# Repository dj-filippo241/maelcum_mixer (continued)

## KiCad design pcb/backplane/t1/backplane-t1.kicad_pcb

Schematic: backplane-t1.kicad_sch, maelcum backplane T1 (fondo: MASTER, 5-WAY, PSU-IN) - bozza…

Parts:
C1, C3, C5, C7, C9, C11, C13, C15, C17, C19, C21, C23, C25, C27, C29, C31, C33, C35, C37, C39, C41, C43, C45, C47, C49, C51, C53, C55: 100n 50V; C_0805_2012Metric
C2, C4, C6, C8, C10, C12, C14, C16, C18, C20, C22, C24, C26, C28, C30, C32, C34, C36, C38, C40, C42, C44, C46, C48, C50, C52, C54, C56: 10u 50V X7R; C_1206_3216Metric
F1, F2: PTC 0.3 A; Fuse_1812_4532Metric
F3, F4, F5, F6, F7, F8: PTC 0.2 A; Fuse_1812_4532Metric
F9, F14, F19, F24: PTC 0.1 A; Fuse_1812_4532Metric
F10, F12, F15, F17, F20, F22, F25, F27: PTC 0.05 A; Fuse_1812_4532Metric
F11, F13, F16, F18, F21, F23, F26, F28: PTC 0.5 A; Fuse_1812_4532Metric
H1, H2, H3, H4, H5: CHASSIS; MountingHole_3.2mm_M3_Pad
J5W: ponticello J5W; PinHeader_2x02_P2.54mm_Vertical
J5W1: C96 femmina 5W1; DIN41612_C_3x32_Female_Vertical_THT
J5W2: C96 femmina 5W2; DIN41612_C_3x32_Female_Vertical_THT
J5W3: C96 femmina 5W3; DIN41612_C_3x32_Female_Vertical_THT
J5W4: C96 femmina 5W4; DIN41612_C_3x32_Female_Vertical_THT
JC1: cavo C1 T1-T2 (VE); IDC-Header_2x05_P2.54mm_Vertical
JC2: cavo C2 T1-T2 (pilotato); IDC-Header_2x05_P2.54mm_Vertical
JC5: cavo C5 T1-T4 (VE); IDC-Header_2x05_P2.54mm_Vertical
JC6: cavo C6 T1-T4 (pilotato); IDC-Header_2x10_P2.54mm_Vertical
JMAS: C96 femmina MAS; DIN41612_C_3x32_Female_Vertical_THT
JMS: ponticello JMS; PinHeader_2x02_P2.54mm_Vertical
JOUT_L: C96 femmina OUT_L; DIN41612_C_3x32_Female_Vertical_THT
JOUT_R: C96 femmina OUT_R; DIN41612_C_3x32_Female_Vertical_THT
JP2: potenza P2 T1-T2; Molex_Mini-Fit_Jr_5566-10A2_2x05_P4.20mm_Vertical
JP3: potenza P3 T1-T3; Molex_Mini-Fit_Jr_5566-10A2_2x05_P4.20mm_Vertical
JP4: potenza P4 T1-T4; Molex_Mini-Fit_Jr_5566-10A2_2x05_P4.20mm_Vertical
JPSU: C96 femmina PSU; DIN41612_C_3x32_Female_Vertical_THT
JVIE: presa JVIE; PinHeader_1x03_P2.54mm_Vertical

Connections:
5W_OUT_L: J5W.1, J5W1.b4
5W_OUT_R: J5W.3, J5W2.b5
5W_SUM_L: J5W1.b7, J5W3.b7
5W_SUM_R: J5W2.b8, J5W4.b8
+5V: F3.1, F6.1, F9.1, F14.1, F19.1, F24.1, JP2.5, JP3.5, JP4.5, JPSU.a21, JPSU.a22
+5V_5W1: C17.1, C18.1, F9.2, J5W1.a21, J5W1.a22
+5V_5W2: C27.1, C28.1, F14.2, J5W2.a21, J5W2.a22
+5V_5W3: C37.1, C38.1, F19.2, J5W3.a21, J5W3.a22
+5V_5W4: C47.1, C48.1, F24.2, J5W4.a21, J5W4.a22
+5V_OUT_L: C5.1, C6.1, F3.2, JOUT_L.a21, JOUT_L.a22
+5V_OUT_R: C11.1, C12.1, F6.2, JOUT_R.a21, JOUT_R.a22
AC_OK: JOUT_L.c17, JPSU.c17
AGND: C1.2, C2.2, C3.1, C4.1, C5.2, C6.2, C7.2, C8.2, C9.1, C10.1, C11.2, C12.2, C13.2, C14.2, C15.1, C16.1, C17.2, C18.2, C19.2, C20.2, C21.2, C22.2, C23.1, C24.1, C25.1, C26.1, C27.2, C28.2, C29.2, C30.2, C31.2, C32.2, C33.1, C34.1, C35.1, C36.1, C37.2, C38.2, C39.2, C40.2, C41.2, C42.2, C43.1, C44.1, C45.1, C46.1, C47.2, C48.2, C49.2, C50.2, C51.2, C52.2, C53.1, C54.1, C55.1, C56.1, J5W1.a13, J5W1.a14, J5W1.a15, J5W1.a16, J5W1.a17, J5W1.a18, J5W1.a19, J5W1.a20, J5W1.b3, J5W1.b6, J5W1.b9, J5W1.b12, J5W1.b15, J5W1.b18, J5W1.b21, J5W1.b24, J5W1.b27, J5W1.b30, J5W2.a13, J5W2.a14, J5W2.a15, J5W2.a16, J5W2.a17, J5W2.a18, J5W2.a19, J5W2.a20, J5W2.b3, J5W2.b6, J5W2.b9, J5W2.b12, J5W2.b15, J5W2.b18, J5W2.b21, J5W2.b24, J5W2.b27, J5W2.b30, J5W3.a13, J5W3.a14, J5W3.a15, J5W3.a16, J5W3.a17, J5W3.a18, J5W3.a19, J5W3.a20, J5W3.b3, J5W3.b6, J5W3.b9, J5W3.b12, J5W3.b15, J5W3.b18, J5W3.b21, J5W3.b24, J5W3.b27, J5W3.b30, J5W4.a13, J5W4.a14, J5W4.a15, J5W4.a16, J5W4.a17, J5W4.a18, J5W4.a19, J5W4.a20, J5W4.b3, J5W4.b6, J5W4.b9, J5W4.b12, J5W4.b15, J5W4.b18, J5W4.b21, J5W4.b24, J5W4.b27, J5W4.b30, JC1.1, JC1.3, JC1.5, JC1.6, JC1.7, JC1.8, JC1.9, JC1.10, JC2.1, JC2.3, JC2.7, JC2.8, JC2.9, JC2.10, JC5.1, JC5.3, JC5.5, JC5.7, JC5.9, JC5.10, JC6.1, JC6.3, JC6.5, JC6.7, JC6.9, JC6.11, JC6.13, JC6.15, JC6.19, JC6.20, JMAS.a13, JMAS.a14, JMAS.a15, JMAS.a16, JMAS.a17, JMAS.a18, JMAS.a19, JMAS.a20, JMAS.b3, JMAS.b6, JMAS.b9, JMAS.b12, JMAS.b15, JMAS.b18, JMAS.b21, JMAS.b24, JMAS.b27, JMAS.b30, JOUT_L.a13, JOUT_L.a14, JOUT_L.a15, JOUT_L.a16, JOUT_L.a17, JOUT_L.a18, JOUT_L.a19, JOUT_L.a20, JOUT_R.a13, JOUT_R.a14, JOUT_R.a15, JOUT_R.a16, JOUT_R.a17, JOUT_R.a18, JOUT_R.a19, JOUT_R.a20, JP2.6, JP2.7, JP2.8, JP3.6, JP3.7, JP3.8, JP4.6, JP4.7, JP4.8, JPSU.a13, JPSU.a14, JPSU.a15, JPSU.a16, JPSU.a17, JPSU.a18, JPSU.a19, JPSU.a20, JVIE.2
CHASSIS: H1.1, H2.1, H3.1, H4.1, H5.1, J5W1.a25, J5W1.a26, J5W2.a25, J5W2.a26, J5W3.a25, J5W3.a26, J5W4.a25, J5W4.a26, JMAS.a25, JMAS.a26, JOUT_L.a25, JOUT_L.a26, JOUT_R.a25, JOUT_R.a26, JP2.10, JP3.10, JP4.10, JPSU.a25, JPSU.a26
CTRL_GND: J5W1.a23, J5W1.a24, J5W1.c16, J5W1.c20, J5W1.c24, J5W1.c28, J5W2.a23, J5W2.a24, J5W2.c16, J5W2.c20, J5W2.c24, J5W2.c28, J5W3.a23, J5W3.a24, J5W3.c16, J5W3.c20, J5W3.c24, J5W3.c28, J5W4.a23, J5W4.a24, J5W4.c16, J5W4.c20, J5W4.c24, J5W4.c28, JC2.5, JC6.17, JMAS.c16, JMAS.c20, JMAS.c24, JMAS.c28, JOUT_L.a23, JOUT_L.a24, JOUT_L.c16, JOUT_L.c20, JOUT_L.c24, JOUT_L.c28, JOUT_R.a23, JOUT_R.a24, JOUT_R.c16, JOUT_R.c20, JOUT_R.c24, JOUT_R.c28, JP2.9, JP3.9, JP4.9, JPSU.a23, JPSU.a24, JPSU.c16, JPSU.c20, JPSU.c24, JPSU.c28
DJBUS_L: J5W3.b1, JC1.2
DJBUS_R: J5W4.b2, JC1.4
GLOBAL_MUTE: JC2.6, JC6.18, JOUT_L.c9, JOUT_R.c9
INS_RET_L: JMAS.b28, JMS.2
INS_RET_R: JMAS.b29, JMS.4
INS_SEND_L: JMAS.b25, JMS.1
INS_SEND_R: JMAS.b26, JMS.3
MON_L: JC2.2, JMAS.b22
MON_R: JC2.4, JMAS.b23
MSUM1_L: J5W.2, JMAS.b1
MSUM1_R: J5W.4, JMAS.b2
MSUM2_L: JC6.2, JMAS.b4
MSUM2_R: JC6.4, JMAS.b5
MSUM3_L: JC6.6, JMAS.b7
MSUM3_R: JC6.8, JMAS.b8
MSUM4_L: JC6.10, JMAS.b10
MSUM4_R: JC6.12, JMAS.b11
MSUM5_L: JC6.14, JMAS.b13
MSUM5_R: JC6.16, JMAS.b14
MSUM6_L: JC5.2, JMAS.b16
MSUM6_R: JC5.4, JMAS.b17
MSUM7_L: JC5.6, JMAS.b19
MSUM7_R: JC5.8, JMAS.b20
RAW+22: F10.1, F15.1, F20.1, F25.1, JOUT_L.a5, JOUT_L.a6, JP2.3, JP3.3, JP4.3, JPSU.a5, JPSU.a6
RAW+22_5W1: C19.1, C20.1, F10.2, J5W1.a5, J5W1.a6
RAW+22_5W2: C29.1, C30.1, F15.2, J5W2.a5, J5W2.a6
RAW+22_5W3: C39.1, C40.1, F20.2, J5W3.a5, J5W3.a6
RAW+22_5W4: C49.1, C50.1, F25.2, J5W4.a5, J5W4.a6
RAW+26: F4.1, F7.1, JPSU.a9, JPSU.a10
RAW+26_OUT_L: C7.1, C8.1, F4.2, JOUT_L.a9, JOUT_L.a10
RAW+26_OUT_R: C13.1, C14.1, F7.2, JOUT_R.a9, JOUT_R.a10
RAW+27: F1.1, F11.1, F16.1, F21.1, F26.1, JP2.1, JP3.1, JP4.1, JPSU.a1, JPSU.a2
RAW+27_5W1: C21.1, C22.1, F11.2, J5W1.a1, J5W1.a2
RAW+27_5W2: C31.1, C32.1, F16.2, J5W2.a1, J5W2.a2
RAW+27_5W3: C41.1, C42.1, F21.2, J5W3.a1, J5W3.a2
RAW+27_5W4: C51.1, C52.1, F26.2, J5W4.a1, J5W4.a2
RAW+27_MAS: C1.1, C2.1, F1.2, JMAS.a1, JMAS.a2
RAW-22: F12.1, F17.1, F22.1, F27.1, JP2.4, JP3.4, JP4.4, JPSU.a7, JPSU.a8
RAW-22_5W1: C23.2, C24.2, F12.2, J5W1.a7, J5W1.a8
RAW-22_5W2: C33.2, C34.2, F17.2, J5W2.a7, J5W2.a8
RAW-22_5W3: C43.2, C44.2, F22.2, J5W3.a7, J5W3.a8
RAW-22_5W4: C53.2, C54.2, F27.2, J5W4.a7, J5W4.a8
RAW-26: F5.1, F8.1, JPSU.a11, JPSU.a12
RAW-26_OUT_L: C9.2, C10.2, F5.2, JOUT_L.a11, JOUT_L.a12
RAW-26_OUT_R: C15.2, C16.2, F8.2, JOUT_R.a11, JOUT_R.a12
RAW-27: F2.1, F13.1, F18.1, F23.1, F28.1, JP2.2, JP3.2, JP4.2, JPSU.a3, JPSU.a4
RAW-27_5W1: C25.2, C26.2, F13.2, J5W1.a3, J5W1.a4
RAW-27_5W2: C35.2, C36.2, F18.2, J5W2.a3, J5W2.a4
RAW-27_5W3: C45.2, C46.2, F23.2, J5W3.a3, J5W3.a4
RAW-27_5W4: C55.2, C56.2, F28.2, J5W4.a3, J5W4.a4
RAW-27_MAS: C3.2, C4.2, F2.2, JMAS.a3, JMAS.a4
VIE_TAP_L: JMAS.b31, JVIE.1
VIE_TAP_R: JMAS.b32, JVIE.3

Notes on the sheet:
SLOT MAS (master)
SLOT OUT_L (uscita)
SLOT OUT_R (uscita)
SLOT 5W1 (5way)
SLOT 5W2 (5way)
SLOT 5W3 (5way)
SLOT 5W4 (5way)
SLOT PSU (psu-in)
CAVO C1
CAVO C2
CAVO C5
CAVO C6
POTENZA P2
POTENZA P3
POTENZA P4
PONTICELLI

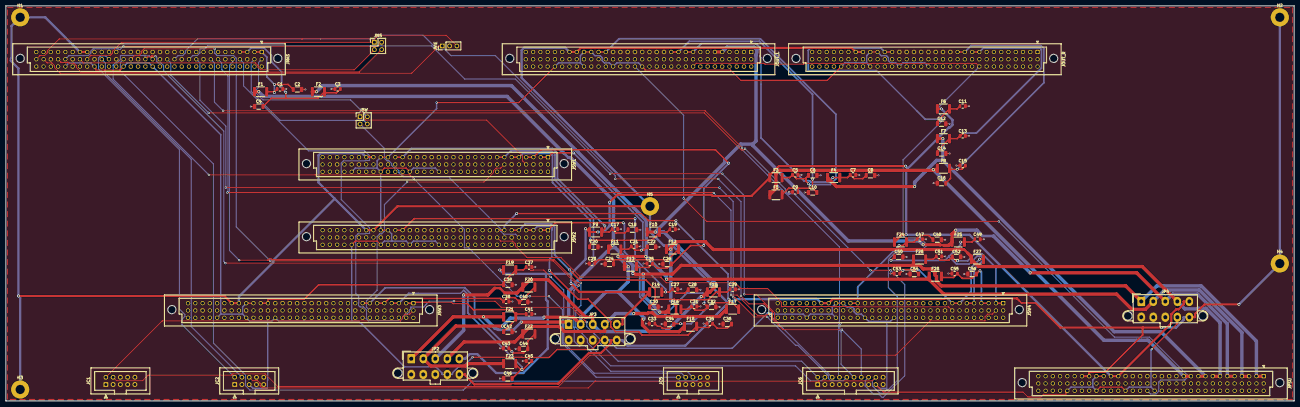
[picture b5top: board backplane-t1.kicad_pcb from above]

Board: 4 copper layers, 450.0 x 138.0 mm, 107 parts (0 on the bottom side), 68 nets.

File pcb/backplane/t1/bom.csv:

quantita;valore;impronta;riferimenti;nota
28;100n 50V;C_0805_2012Metric;C1 C3 C5 C7 C9 C11 C13 C15 C17 C19 C21 C23 C25 C27 C29 C31 C33 C35 C37 C39 C41 C43 C45 C47 C49 C51 C53 C55;bypass di slot (backplane §8)
28;10u 50V X7R;C_1206_3216Metric;C2 C4 C6 C8 C10 C12 C14 C16 C18 C20 C22 C24 C26 C28 C30 C32 C34 C36 C38 C40 C42 C44 C46 C48 C50 C52 C54 C56;bulk di slot (backplane §8); NOTA: MLCC 50 V
2;PTC 0.3 A;Fuse_1812_4532Metric;F1 F2;PTC di slot (psu-esterno §4.3); NOTA: tenuta 0.3 A, >= 33 V, 1812
8;PTC 0.05 A;Fuse_1812_4532Metric;F10 F12 F15 F17 F20 F22 F25 F27;PTC di slot (psu-esterno §4.3); NOTA: tenuta 0.05 A, >= 33 V, 1812
8;PTC 0.5 A;Fuse_1812_4532Metric;F11 F13 F16 F18 F21 F23 F26 F28;PTC di slot (psu-esterno §4.3); NOTA: tenuta 0.5 A, >= 33 V, 1812
6;PTC 0.2 A;Fuse_1812_4532Metric;F3 F4 F5 F6 F7 F8;PTC di slot (psu-esterno §4.3); NOTA: tenuta 0.2 A, >= 33 V, 1812
4;PTC 0.1 A;Fuse_1812_4532Metric;F9 F14 F19 F24;PTC di slot (psu-esterno §4.3); NOTA: tenuta 0.1 A, >= 33 V, 1812
1;ponticello J5W;PinHeader_2x02_P2.54mm_Vertical;J5W;ponticello di continuità (dec. 111): 5-way -> MSUM1 (EQ grafico dopo il 5-way); due cavallotti 1-2 e 3-4
1;C96 femmina 5W1;DIN41612_C_3x32_Female_Vertical_THT;J5W1;slot 5W1, classe 5way; pin da pcb/five-way/LB (netlist). Fila a a 2.11 mm dal piano medio della scheda di modulo, lato F del modulo verso la fila c (Harting 09 03 196 6921)
1;C96 femmina 5W2;DIN41612_C_3x32_Female_Vertical_THT;J5W2;slot 5W2, classe 5way; pin da pcb/five-way/RB (netlist). Fila a a 2.11 mm dal piano medio della scheda di modulo, lato F del modulo verso la fila c (Harting 09 03 196 6921)
1;C96 femmina 5W3;DIN41612_C_3x32_Female_Vertical_THT;J5W3;slot 5W3, classe 5way; pin da pcb/five-way/LA (netlist). Fila a a 2.11 mm dal piano medio della scheda di modulo, lato F del modulo verso la fila c (Harting 09 03 196 6921)
1;C96 femmina 5W4;DIN41612_C_3x32_Female_Vertical_THT;J5W4;slot 5W4, classe 5way; pin da pcb/five-way/RA (netlist). Fila a a 2.11 mm dal piano medio della scheda di modulo, lato F del modulo verso la fila c (Harting 09 03 196 6921)
1;cavo C1 T1-T2 (VE);IDC-Header_2x05_P2.54mm_Vertical;JC1;NOTA: cavo piatto, ogni segnale fra due fili di massa; solo net a massa virtuale
1;cavo C2 T1-T2 (pilotato);IDC-Header_2x05_P2.54mm_Vertical;JC2;NOTA: cavo piatto, ogni segnale fra due fili di massa; solo linee pilotate
1;cavo C5 T1-T4 (VE);IDC-Header_2x05_P2.54mm_Vertical;JC5;NOTA: cavo piatto, ogni segnale fra due fili di massa; solo net a massa virtuale
1;cavo C6 T1-T4 (pilotato);IDC-Header_2x10_P2.54mm_Vertical;JC6;NOTA: cavo piatto, ogni segnale fra due fili di massa; solo linee pilotate
1;C96 femmina MAS;DIN41612_C_3x32_Female_Vertical_THT;JMAS;slot MAS, classe master; pin da pcb/master/segnale (netlist). Fila a a 2.11 mm dal piano medio della scheda di modulo, lato F del modulo verso la fila c (Harting 09 03 196 6921)
1;ponticello JMS;PinHeader_2x02_P2.54mm_Vertical;JMS;ponticello di continuità (dec. 111): inserzione del master (EQ grafico); due cavallotti 1-2 e 3-4
1;C96 femmina OUT_L;DIN41612_C_3x32_Female_Vertical_THT;JOUT_L;slot OUT_L, classe uscita; pin da pcb/master/uscita-L (netlist). Fila a a 2.11 mm dal piano medio della scheda di modulo, lato F del modulo verso la fila c (Harting 09 03 196 6921)
1;C96 femmina OUT_R;DIN41612_C_3x32_Female_Vertical_THT;JOUT_R;slot OUT_R, classe uscita; pin da pcb/master/uscita-R (netlist). Fila a a 2.11 mm dal piano medio della scheda di modulo, lato F del modulo verso la fila c (Harting 09 03 196 6921)
1;potenza P2 T1-T2;Molex_Mini-Fit_Jr_5566-10A2_2x05_P4.20mm_Vertical;JP2;NOTA: Mini-Fit Jr 2x5; radiale AGND del tratto fino alla stella del PSU-IN (grounding §2)
1;potenza P3 T1-T3;Molex_Mini-Fit_Jr_5566-10A2_2x05_P4.20mm_Vertical;JP3;NOTA: Mini-Fit Jr 2x5; radiale AGND del tratto fino alla stella del PSU-IN (grounding §2)
1;potenza P4 T1-T4;Molex_Mini-Fit_Jr_5566-10A2_2x05_P4.20mm_Vertical;JP4;NOTA: Mini-Fit Jr 2x5; radiale AGND del tratto fino alla stella del PSU-IN (grounding §2)
1;C96 femmina PSU;DIN41612_C_3x32_Female_Vertical_THT;JPSU;slot PSU, classe psu-in; pin da pcb/psu-in (netlist). Fila a a 2.11 mm dal piano medio della scheda di modulo, lato F del modulo verso la fila c (Harting 09 03 196 6921)
1;presa JVIE;PinHeader_1x03_P2.54mm_Vertical;JVIE;NOTA: predisposizione VIE_TAP del master (UTIL-VIE, dec. 111), nessuno slot nella disposizione F

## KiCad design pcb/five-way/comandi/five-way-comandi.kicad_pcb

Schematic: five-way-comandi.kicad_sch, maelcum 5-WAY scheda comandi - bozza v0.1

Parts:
C1: 100p C0G; C_0805_2012Metric
C2: 220n film; C_1812_4532Metric
C3, C6, C7: 100n film; C_1812_4532Metric
C4, C10, C16, C22, C26, C28: 47p C0G; C_0805_2012Metric
C5, C11, C17, C23, C27, C29: 100n C0G; C_1206_3216Metric
C8: 47n film; C_1812_4532Metric
C9, C12, C13: 22n C0G; C_1206_3216Metric
C14: 10n C0G; C_1206_3216Metric
C15, C18, C19: 4n7 C0G; C_1206_3216Metric
C20: 2n2 C0G; C_1206_3216Metric
C21, C24, C25: 1n C0G; C_1206_3216Metric
C30, C31, C32, C33, C34, C35, C36, C37, C38, C39, C40, C41, C42, C43, C44, C45, C47, C49, C51, C53, C55, C59: 100n; C_0805_2012Metric
C46, C48, C50, C52, C54: 1u 25V; C_1206_3216Metric
C56, C57, C58: 10u 25V; C_1206_3216Metric
C60: 2u2 16V; C_1206_3216Metric
D1, D2, D3, D4, D5: LED bicolore VR 3 mm; LED_D3.0mm-3
D6, D7, D8, D9, D10, D11, D12, D13, D14, D15, D16: 1N4148W; D_SOD-123
D17, D18, D19, D20, D21, D22, D23, D24, D25, D26: LED 5x2; LED_Rectangular_W5.0mm_H2.0mm
J1: 2x31 cavo piatto; PinHeader_2x31_P2.54mm_Vertical
J2: 2x28 cavo piatto; PinHeader_2x28_P2.54mm_Vertical
J3, J4: 2x3 cavo piatto; PinHeader_2x03_P2.54mm_Vertical
Q1, Q2, Q3, Q4, Q5: 2N7002; SOT-23
R1, R2, R20: 20k 0.1%; R_0805_2012Metric
R3: 5k76 0.1%; R_0805_2012Metric
R4, R5: 17k8 0.1%; R_0805_2012Metric
R6, R12, R18, R24, R28, R30, R40, R41, R44, R45, R48, R49, R52, R53, R56, R57: 1k; R_0805_2012Metric
R7, R13, R19, R25, R29, R31: 3M; R_0805_2012Metric
R8: 18k7 0.1%; R_0805_2012Metric
R9: 37k4 0.1%; R_0805_2012Metric
R10, R11, R16, R17: 19k6 0.1%; R_0805_2012Metric
R14: 20k5 0.1%; R_0805_2012Metric
R15: 41k2 0.1%; R_0805_2012Metric
R21: 40k2 0.1%; R_0805_2012Metric
R22, R23: 13k3 0.1%; R_0805_2012Metric
R26: 14k 0.1%; R_0805_2012Metric
R27: 28k 0.1%; R_0805_2012Metric
R32: 127k 0.1%; R_0805_2012Metric
R33: 12k7 0.1%; R_0805_2012Metric
R34: 12k4 0.1%; R_0805_2012Metric
R35: 402 0.1%; R_0805_2012Metric
R36, R37, R39, R43, R47, R51, R55: 10k; R_0805_2012Metric
R38, R42, R46, R50, R54: 750k; R_0805_2012Metric
R58: 6k2; R_0805_2012Metric
RV1, RV4, RV7, RV10, RV13: 10k lin doppio, scatto; Potentiometer_Alps_RK09L_Double_Vertical
RV2, RV5, RV8, RV11, RV14: 10k lin; Potentiometer_Alps_RK09L_Single_Vertical
RV3, RV6, RV9, RV12, RV15: 1k log doppio; Potentiometer_Alps_RK09L_Double_Vertical
RV16: 10k/10k/5k lin x2; PinHeader_2x09_P2.54mm_Vertical
RV17: 10k/5k log A x2; PinHeader_2x06_P2.54mm_Vertical
SW1, SW2, SW3, SW4, SW5: levetta FISSO/MOLLA; SW_NKK_G1xJP
U1: LM3915N-1; DIP-18_W7.62mm
U101, U102, U103, U104, U105, U106: OPA1654AIDR; SOIC-14_3.9x8.7mm_P1.27mm
U107, U108, U109, U110, U111: LM339DR; SOIC-14_3.9x8.7mm_P1.27mm

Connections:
5W_MET_L: J1.55, R1.1
5W_MET_R: J2.55, R2.1
+5VF: C47.1, C49.1, C51.1, C53.1, C55.1, C58.1, C59.1, C60.1, D1.2 (A), D2.2 (A), D3.2 (A), D4.2 (A), D5.2 (A), D17.2 (A), D18.2 (A), D19.2 (A), D20.2 (A), D21.2 (A), D22.2 (A), D23.2 (A), D24.2 (A), D25.2 (A), D26.2 (A), J1.60, R36.1, R38.1, R39.1, R42.1, R43.1, R46.1, R47.1, R50.1, R51.1, R54.1, R55.1, U1.3 (V+), U1.9 (MODE), U107.3 (VCC), U108.3 (VCC), U109.3 (VCC), U110.3 (VCC), U111.3 (VCC)
+15LN: C30.1, C32.1, C34.1, C36.1, C38.1, C40.1, C56.1, J1.57, R32.1, U101.4 (V+), U102.4 (V+), U103.4 (V+), U104.4 (V+), U105.4 (V+), U106.4 (V+)
+REF5: J1.2, RV2.3 (CW), RV5.3 (CW), RV8.3 (CW), RV11.3 (CW), RV14.3 (CW), U1.6 (RHI)
-15LN: C31.2, C33.2, C35.2, C37.2, C39.2, C41.2, C57.2, J1.59, U101.11 (V-), U102.11 (V-), U103.11 (V-), U104.11 (V-), U105.11 (V-), U106.11 (V-)
AGND: C3.2, C5.2, C9.2, C11.2, C15.2, C17.2, C21.2, C23.2, C27.2, C29.2, C30.2, C31.1, C32.2, C33.1, C34.2, C35.1, C36.2, C37.1, C38.2, C39.1, C40.2, C41.1, C42.2, C43.2, C44.2, C56.2, C57.1, J1.1, J1.10, J1.18, J1.26, J1.34, J1.42, J1.49, J1.54, J1.56, J1.58, J1.62, R7.2, R9.2, R13.2, R15.2, R19.2, R21.2, R25.2, R27.2, R29.2, R31.2, R35.2, RV2.1 (CCW), RV5.1 (CCW), RV8.1 (CCW), RV11.1 (CCW), RV14.1 (CCW), RV16.1 (S1_CCW), RV17.1 (S1_CCW), U1.4 (RLO), U101.3 (+), U106.5 (+), U106.10 (+), U106.12 (+)
AGNDR: J2.1, J2.10, J2.18, J2.26, J2.34, J2.42, J2.49, J2.54, J2.56, RV16.10 (S4_CCW), RV17.7 (S3_CCW)
AH2: R8.2, R10.1, U102.1, U102.2 (-)
AH3: R14.2, R16.1, U103.1, U103.2 (-)
AH4: R20.2, R22.1, U104.1, U104.2 (-)
AH5: R26.2, U105.1, U105.2 (-), U105.5 (+)
AH21: C6.2, C7.1, R8.1
AH22: C7.2, R9.1, U102.3 (+)
AH31: C12.2, C13.1, R14.1
AH32: C13.2, R15.1, U103.3 (+)
AH41: C18.2, C19.1, R20.1
AH42: C19.2, R21.1, U104.3 (+)
AH51: C24.2, C25.1, R26.1
AH52: C25.2, R27.1, U105.3 (+)
AL1: C2.2, U101.6 (-), U101.7, U101.10 (+)
AL2: C8.2, U102.6 (-), U102.7, U102.10 (+)
AL3: C14.2, U103.6 (-), U103.7, U103.10 (+)
AL4: C20.2, U104.6 (-), U104.7, U104.10 (+)
AL11: C2.1, R4.2, R5.1
AL12: C3.1, R5.2, U101.5 (+)
AL21: C8.1, R10.2, R11.1
AL22: C9.1, R11.2, U102.5 (+)
AL31: C14.1, R16.2, R17.1
AL32: C15.1, R17.2, U103.5 (+)
AL41: C20.1, R22.2, R23.1
AL42: C21.1, R23.2, U104.5 (+)
BPB1: J1.4, RV3.3 (A_CW)
BPB1R: J2.4, RV3.6 (B_CW)
BPB2: J1.12, RV6.3 (A_CW)
BPB2R: J2.12, RV6.6 (B_CW)
BPB3: J1.20, RV9.3 (A_CW)
BPB3R: J2.20, RV9.6 (B_CW)
BPB4: J1.28, RV12.3 (A_CW)
BPB4R: J2.28, RV12.6 (B_CW)
BPB5: J1.36, RV15.3 (A_CW)
BPB5R: J2.36, RV15.6 (B_CW)
CTRL_GND: C45.2, C46.2, C47.2, C48.2, C49.2, C50.2, C51.2, C52.2, C53.2, C54.2, C55.2, C58.2, C59.2, C60.2, J1.61, R37.2, R58.2, U1.2 (V-), U1.8 (REFADJ), U107.12 (GND), U108.12 (GND), U109.12 (GND), U110.12 (GND), U111.12 (GND)
CTRL_GND_A_L: J3.6, SW1.2 (A_COM), SW2.2 (A_COM), SW3.2 (A_COM), SW4.2 (A_COM), SW5.2 (A_COM)
CTRL_GND_A_R: J4.6, SW1.5 (B_COM), SW2.5 (B_COM), SW3.5 (B_COM), SW4.5 (B_COM), SW5.5 (B_COM)
DAHIGH: D9.2 (A), R24.2
DAKICK: D7.2 (A), R12.2
DAM: D11.2 (A), R30.2
DAMID: D8.2 (A), R18.2
DASUB: D6.2 (A), R6.2
DASUPER: D10.2 (A), R28.2
DDG: J1.43, RV16.3 (S1_CW)
DDGR: J2.43, RV16.12 (S4_CW)
DOHIGH: C22.1, R24.1, U104.8
DOKICK: C10.1, R12.1, U102.8
DOM: C28.1, R30.1, U105.14
DOMID: C16.1, R18.1, U103.8
DOSUB: C4.1, R6.1, U101.8
DOSUPER: C26.1, R28.1, U105.7
DQ1: J1.7, RV1.3 (A_CW)
DQ1R: J2.7, RV1.6 (B_CW)
DQ2: J1.15, RV4.3 (A_CW)
DQ2R: J2.15, RV4.6 (B_CW)
DQ3: J1.23, RV7.3 (A_CW)
DQ3R: J2.23, RV7.6 (B_CW)
DQ4: J1.31, RV10.3 (A_CW)
DQ4R: J2.31, RV10.6 (B_CW)
DQ5: J1.39, RV13.3 (A_CW)
DQ5R: J2.39, RV13.6 (B_CW)
DTP: J1.50, RV17.3 (S1_CW)
DTPR: J2.50, RV17.9 (S3_CW)
DWG: J1.44, RV16.2 (S1_W)
DWGR: J2.44, RV16.11 (S4_W)
DWT: J1.51, RV17.2 (S1_W)
DWTR: J2.51, RV17.8 (S3_W)
GFHIGH: Q4.3 (D), R53.2
GFKICK: Q2.3 (D), R45.2
GFMID: Q3.3 (D), R49.2
GFSUB: Q1.3 (D), R41.2
GFSUPER: Q5.3 (D), R57.2
GLOW: J1.45, RV16.6 (S2_CW)
GLOWR: J2.45, RV16.15 (S5_CW)
GLR: J1.46, RV16.4 (S2_CCW), RV16.5 (S2_W)
GLRR: J2.46, RV16.13 (S5_CCW), RV16.14 (S5_W)
GMID: J1.47, RV16.9 (S3_CW)
GMIDR: J2.47, RV16.18 (S6_CW)
GMR: J1.48, RV16.7 (S3_CCW), RV16.8 (S3_W)
GMRR: J2.48, RV16.16 (S6_CCW), RV16.17 (S6_W)
GW1: J1.8, RV1.2 (A_W)
GW1R: J2.8, RV1.5 (B_W)
GW2: J1.16, RV4.2 (A_W)
GW2R: J2.16, RV4.5 (B_W)
GW3: J1.24, RV7.2 (A_W)
GW3R: J2.24, RV7.5 (B_W)
GW4: J1.32, RV10.2 (A_W)
GW4R: J2.32, RV10.5 (B_W)
GW5: J1.40, RV13.2 (A_W)
GW5R: J2.40, RV13.5 (B_W)
HOHIGH: C22.2, C23.1, D9.1 (K), R25.1, U104.9 (-), U104.12 (+)
HOKICK: C10.2, C11.1, D7.1 (K), R13.1, U102.9 (-), U102.12 (+)
HOM: C28.2, C29.1, D11.1 (K), R31.1, U105.13 (-), U106.3 (+)
HOMID: C16.2, C17.1, D8.1 (K), R19.1, U103.9 (-), U103.12 (+)
HOSUB: C4.2, C5.1, D6.1 (K), R7.1, U101.9 (-), U101.12 (+)
HOSUPER: C26.2, C27.1, D10.1 (K), R29.1, U105.6 (-), U105.10 (+)
KGHIGH: Q4.2 (S), U110.13 (4OUT)
KGKICK: Q2.2 (S), U108.13 (4OUT)
KGMID: Q3.2 (S), U109.13 (4OUT)
KGSUB: Q1.2 (S), U107.13 (4OUT)
KGSUPER: Q5.2 (S), U111.13 (4OUT)
KRHIGH: D15.2 (A), R52.2, U110.14 (3OUT)
KRKICK: D13.2 (A), R44.2, U108.14 (3OUT)
KRMID: D14.2 (A), R48.2, U109.14 (3OUT)
KRSUB: D12.2 (A), R40.2, U107.14 (3OUT)
KRSUPER: D16.2 (A), R56.2, U111.14 (3OUT)
KSW1_L: J3.1, SW1.1 (A1), SW1.3 (A3)
KSW1_R: J4.1, SW1.4 (B3), SW1.6 (B1)
KSW2_L: J3.2, SW2.1 (A1), SW2.3 (A3)
KSW2_R: J4.2, SW2.4 (B3), SW2.6 (B1)
KSW3_L: J3.3, SW3.1 (A1), SW3.3 (A3)
KSW3_R: J4.3, SW3.4 (B3), SW3.6 (B1)
KSW4_L: J3.4, SW4.1 (A1), SW4.3 (A3)
KSW4_R: J4.4, SW4.4 (B3), SW4.6 (B1)
KSW5_L: J3.5, SW5.1 (A1), SW5.3 (A3)
KSW5_R: J4.5, SW5.4 (B3), SW5.6 (B1)
LEDG1: D1.1 (K_VERDE), R41.1
LEDG2: D2.1 (K_VERDE), R45.1
LEDG3: D3.1 (K_VERDE), R49.1
LEDG4: D4.1 (K_VERDE), R53.1
LEDG5: D5.1 (K_VERDE), R57.1
LEDR1: D1.3 (K_ROSSO), R40.1
LEDR2: D2.3 (K_ROSSO), R44.1
LEDR3: D3.3 (K_ROSSO), R48.1
LEDR4: D4.3 (K_ROSSO), R52.1
LEDR5: D5.3 (K_ROSSO), R56.1
LQHIGH: D15.1 (K), Q4.1 (G), R51.2, U110.2 (2OUT)
LQKICK: D13.1 (K), Q2.1 (G), R43.2, U108.2 (2OUT)
LQMID: D14.1 (K), Q3.1 (G), R47.2, U109.2 (2OUT)
LQSUB: D12.1 (K), Q1.1 (G), R39.2, U107.2 (2OUT)
LQSUPER: D16.1 (K), Q5.1 (G), R55.2, U111.2 (2OUT)
LSN: J1.53, RV17.5 (S2_W), RV17.6 (S2_CW)
LSNR: J2.53, RV17.11 (S4_W), RV17.12 (S4_CW)
LSP: J1.52, RV17.4 (S2_CCW)
LSPR: J2.52, RV17.10 (S4_CCW)
LTHIGH: C52.1, R50.2, U110.1 (1OUT), U110.5 (2IN+)
LTKICK: C48.1, R42.2, U108.1 (1OUT), U108.5 (2IN+)
LTMID: C50.1, R46.2, U109.1 (1OUT), U109.5 (2IN+)
LTSUB: C46.1, R38.2, U107.1 (1OUT), U107.5 (2IN+)
LTSUPER: C54.1, R54.2, U111.1 (1OUT), U111.5 (2IN+)
MET: U1.5 (SIG), U106.1, U106.2 (-)
METHIGH: U104.13 (-), U104.14, U110.6 (1IN-), U110.8 (3IN-), U110.10 (4IN-)
METKICK: U102.13 (-), U102.14, U108.6 (1IN-), U108.8 (3IN-), U108.10 (4IN-)
METMID: U103.13 (-), U103.14, U109.6 (1IN-), U109.8 (3IN-), U109.10 (4IN-)
METSUB: U101.13 (-), U101.14, U107.6 (1IN-), U107.8 (3IN-), U107.10 (4IN-)
METSUPER: U105.8, U105.9 (-), U111.6 (1IN-), U111.8 (3IN-), U111.10 (4IN-)
MKM_1: D17.1 (K), U1.1 (LED1)
MKM_2: D18.1 (K), U1.18 (LED2)
MKM_3: D19.1 (K), U1.17 (LED3)
MKM_4: D20.1 (K), U1.16 (LED4)
MKM_5: D21.1 (K), U1.15 (LED5)
MKM_6: D22.1 (K), U1.14 (LED6)
MKM_7: D23.1 (K), U1.13 (LED7)
MKM_8: D24.1 (K), U1.12 (LED8)
MKM_9: D25.1 (K), U1.11 (LED9)
MKM_10: D26.1 (K), U1.10 (LED10)
MREFM: R58.1, U1.7 (REFOUT)
NDQ1: J1.9, RV1.1 (A_CCW)
NDQ1R: J2.9, RV1.4 (B_CCW)
NDQ2: J1.17, RV4.1 (A_CCW)
NDQ2R: J2.17, RV4.4 (B_CCW)
NDQ3: J1.25, RV7.1 (A_CCW)
NDQ3R: J2.25, RV7.4 (B_CCW)
NDQ4: J1.33, RV10.1 (A_CCW)
NDQ4R: J2.33, RV10.4 (B_CCW)
NDQ5: J1.41, RV13.1 (A_CCW)
NDQ5R: J2.41, RV13.4 (B_CCW)
NUU106_1: U106.6 (-), U106.7
NUU106_2: U106.8, U106.9 (-)
NUU106_3: U106.13 (-), U106.14
POSW1: J1.3, J2.3, RV2.2 (W)
POSW2: J1.11, J2.11, RV5.2 (W)
POSW3: J1.19, J2.19, RV8.2 (W)
POSW4: J1.27, J2.27, RV11.2 (W)
POSW5: J1.35, J2.35, RV14.2 (W)
SNL: C1.1, R1.2, R2.2, R3.1, U101.2 (-)
SOL: C1.2, C6.1, C12.1, C18.1, C24.1, R3.2, R4.1, U101.1, U105.12 (+)
VG: C44.1, R34.2, R35.1, U107.11 (4IN+), U108.11 (4IN+), U109.11 (4IN+), U110.11 (4IN+), U111.11 (4IN+)
VR: C42.1, R32.2, R33.1, U107.7 (1IN+), U108.7 (1IN+), U109.7 (1IN+), U110.7 (1IN+), U111.7 (1IN+)
VTL: C45.1, R36.2, R37.1, U107.4 (2IN-), U108.4 (2IN-), U109.4 (2IN-), U110.4 (2IN-), U111.4 (2IN-)
VY: C43.1, R33.2, R34.1, U107.9 (3IN+), U108.9 (3IN+), U109.9 (3IN+), U110.9 (3IN+), U111.9 (3IN+)
WB1: J1.6, RV3.1 (A_CCW)
WB1R: J2.6, RV3.4 (B_CCW)
WB2: J1.14, RV6.1 (A_CCW)
WB2R: J2.14, RV6.4 (B_CCW)
WB3: J1.22, RV9.1 (A_CCW)
WB3R: J2.22, RV9.4 (B_CCW)
WB4: J1.30, RV12.1 (A_CCW)
WB4R: J2.30, RV12.4 (B_CCW)
WB5: J1.38, RV15.1 (A_CCW)
WB5R: J2.38, RV15.4 (B_CCW)
WW1: J1.5, RV3.2 (A_W)
WW1R: J2.5, RV3.5 (B_W)
WW2: J1.13, RV6.2 (A_W)
WW2R: J2.13, RV6.5 (B_W)
WW3: J1.21, RV9.2 (A_W)
WW3R: J2.21, RV9.5 (B_W)
WW4: J1.29, RV12.2 (A_W)
WW4R: J2.29, RV12.5 (B_W)
WW5: J1.37, RV15.2 (A_W)
WW5R: J2.37, RV15.5 (B_W)

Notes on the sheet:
GAIN, POSITION, WIDTH delle 5 vie (pot doppi: sezione A = L, B = R)
GROWL (6 sezioni) e NASTRO (4 sezioni): pot sul segnale, segnaposto
KILL: levette ON-OFF-(ON) a due poli (polo A = LA, polo B = RA)
LED di livello delle 5 vie (LED bicolore, giallo = verde + rosso)
LED DI LIVELLO: somma L+R, banco d'analisi, rivelatori (five-way-led-livello.md, dec. 177)
LED DI LIVELLO: soglie comuni, latch e comparatori (dec. 177)
METER: un LM3915, 10 LED (zona del 5-way, g = 0,576, RHI = +REF5 della LB)
CAVI: J1 LB, J2 RB, J3 LA, J4 RA (ordine da five-way.py, fili_cavo)

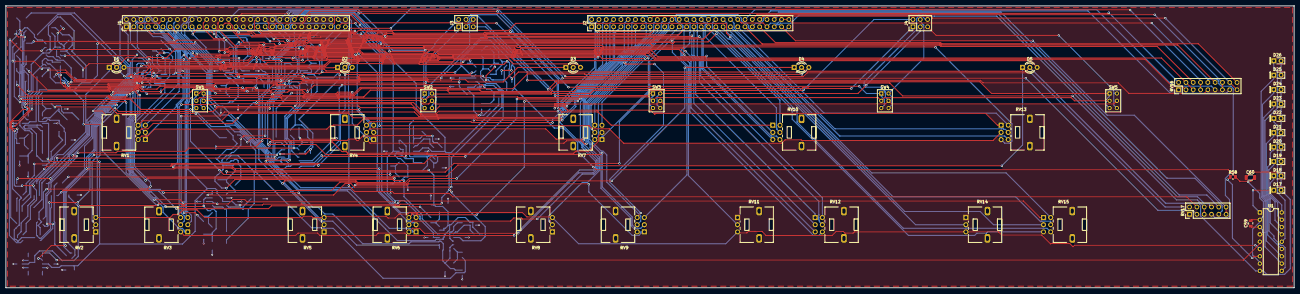
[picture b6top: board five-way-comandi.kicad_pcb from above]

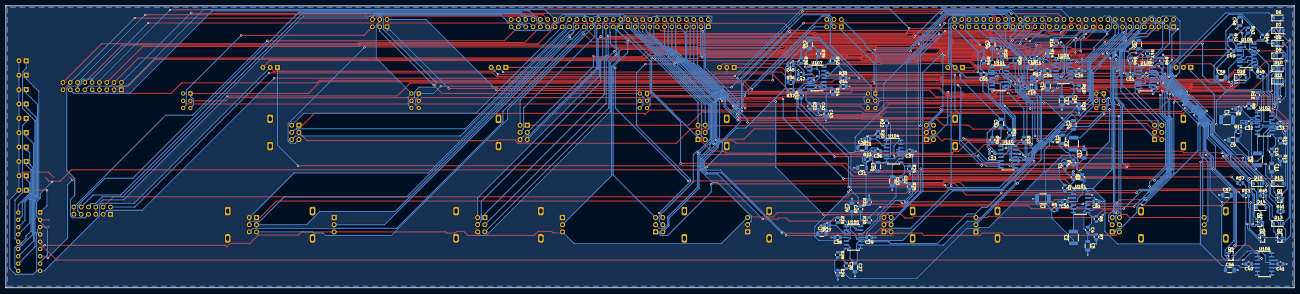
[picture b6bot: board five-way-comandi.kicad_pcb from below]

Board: 4 copper layers, 448.0 x 98.0 mm, 187 parts (142 on the bottom side), 209 nets.

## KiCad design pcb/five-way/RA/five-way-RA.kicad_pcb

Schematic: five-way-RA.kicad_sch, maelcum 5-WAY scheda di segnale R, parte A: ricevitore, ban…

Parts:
C1, C2: 220u 35V; CP_Radial_D8.0mm_P3.50mm
C3: 47u 10V; CP_Radial_D5.0mm_P2.00mm
C4, C8: 10u 35V; CP_Radial_D5.0mm_P2.00mm
C5, C9: 47u 35V; CP_Radial_D6.3mm_P2.50mm
C6, C10: 470u 25V; CP_Radial_D8.0mm_P3.50mm
C7, C11: 100u 25V; CP_Radial_D6.3mm_P2.50mm
C12, C13: 1u 50V; C_1206_3216Metric
C14, C15: 1u 25V; C_1206_3216Metric
C16: 22p C0G; C_0805_2012Metric
C17, C18, C77, C78, C79, C80, C81, C82, C83, C84, C85, C86, C87, C88, C89, C90, C91, C92, C93, C94, C95, C96, C97, C98, C101, C104, C107, C110, C113, C114, C115, C116, C117, C118, C119, C120, C121, C122, C123, C124, C125: 100n; C_0805_2012Metric
C19, C20, C21, C22, C23, C24, C25, C26, C35, C36, C37, C38, C39, C40, C50, C51, C52, C53, C54, C55: 100n film; C_1812_4532Metric
C27, C28, C29, C30, C44, C45, C46, C56, C57, C58, C62, C63, C64, C65, C66, C67: 10n C0G; C_1206_3216Metric
C31, C32, C33, C34, C71, C72, C73, C74, C75, C76: 4n7 C0G; C_1206_3216Metric
C41, C42, C43: 47n film; C_1812_4532Metric
C47, C48, C49, C59, C60, C61, C68, C69, C70: 1n5 C0G; C_1206_3216Metric
C99, C102, C105, C108, C111: 1n C0G; C_0805_2012Metric
C100, C103, C106, C109, C112: 220n; C_0805_2012Metric
D1, D3, D7, D8, D9, D12, D13, D14, D17, D18, D19, D22, D23, D24, D27, D28, D29: 1N4148W; D_SOD-123
D2, D4: S1G; D_SMA
D5, D6, D10, D11, D15, D16, D20, D21, D25, D26: BAT54WS; D_SOD-323
FB1, FB2, FB3, FB4, FB5: ferrite 600R; L_1206_3216Metric
H1, H2, H3: CHASSIS; MountingHole_3.2mm_M3_Pad
J1: C96 maschio; DIN41612_C_3x32_Male_Horizontal_THT
J2: 2x3 cavo piatto; PinHeader_2x03_P2.54mm_Vertical
Q140: BD139; TO-126-3_Vertical
Q141: BD140; TO-126-3_Vertical
R1, R4: 120 1%; R_0805_2012Metric
R2, R5: 1k74 1%; R_0805_2012Metric
R3, R6: 1k; R_0805_2012Metric
R7, R33, R35, R39, R41, R45, R47, R55, R57, R61, R63, R71, R73, R82, R83, R84, R85, R86, R87: 10k 0.1%; R_0805_2012Metric
R8, R9: 20k 0.1%; R_0805_2012Metric
R10, R12, R19, R21, R26, R27, R28, R29, R37, R43, R53, R59, R69: 18k7 0.1%; R_0805_2012Metric
R11, R13: 37k4 0.1%; R_0805_2012Metric
R14, R16, R48, R49, R50, R51: 4k53 0.1%; R_0805_2012Metric
R15, R17: 9k09 0.1%; R_0805_2012Metric
R18, R20, R36, R42, R52, R58, R64, R65, R66, R67, R68: 9k31 0.1%; R_0805_2012Metric
R22, R24, R74, R75, R76, R77: 3k01 0.1%; R_0805_2012Metric
R23, R25: 6k04 0.1%; R_0805_2012Metric
R30: 9k53 0.1%; R_0805_2012Metric
R31: 19k1 0.1%; R_0805_2012Metric
R32: 14k3 0.1%; R_0805_2012Metric
R34, R40, R46, R56, R62, R72: 4k99 0.1%; R_0805_2012Metric
R38, R44, R54, R60, R70: 14k0 0.1%; R_0805_2012Metric
R78, R79, R80, R81: 2k 0.1%; R_0805_2012Metric
R88: 47; R_0805_2012Metric
R89, R97, R105, R113, R121: 22k; R_0805_2012Metric
R90, R98, R106, R114, R122: 10M; R_0805_2012Metric
R91, R95, R96, R99, R103, R104, R107, R111, R112, R115, R119, R120, R123, R127, R128, R129, R130, R131: 10k; R_0805_2012Metric
R92, R100, R108, R116, R124: 2k; R_0805_2012Metric
R93, R94, R101, R102, R109, R110, R117, R118, R125, R126: 100k; R_0805_2012Metric
U1: OPA1612AIDR; SOIC-8_3.9x4.9mm_P1.27mm
U2, U3, U4, U5, U6, U7, U8, U9, U12: OPA1654AIDR; SOIC-14_3.9x8.7mm_P1.27mm
U10, U11: ADG1434YRUZ; TSSOP-20_4.4x6.5mm_P0.65mm
U13, U14: LM339DR; SOIC-14_3.9x8.7mm_P1.27mm
U15, U16, U17, U18: 74HC86PW; TSSOP-14_4.4x5mm_P0.65mm
U19, U20, U21: 74HC14PW; TSSOP-14_4.4x5mm_P0.65mm
U22, U23, U24: 74HC74PW; TSSOP-14_4.4x5mm_P0.65mm
U140: LM317; TO-220-3_Vertical
U141: LM337; TO-220-3_Vertical
U142: 78L15; SOT-89-3
U143: 79L15; SOT-89-3

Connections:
5W_SUM_R: J1.b8, R88.2
+5V: FB5.1, J1.a21, J1.a22
+5VF: C3.1, C114.1, C115.1, C116.1, C117.1, C118.1, C119.1, C120.1, C121.1, C122.1, C123.1, C124.1, C125.1, D6.1 (K), D11.1 (K), D16.1 (K), D21.1 (K), D26.1 (K), FB5.2, R91.1, R95.1, R99.1, R103.1, R107.1, R111.1, R115.1, R119.1, R123.1, R127.1, R129.1, R130.1, R131.1, U13.3 (VCC), U14.3 (VCC), U15.10 (3B), U15.14 (VCC), U16.5 (2B), U16.14 (VCC), U17.2 (1B), U17.13 (4B), U17.14 (VCC), U18.10 (3B), U18.14 (VCC), U19.14 (VCC), U20.14 (VCC), U21.14 (VCC), U22.1 (1CLR), U22.4 (1PRE), U22.10 (2PRE), U22.13 (2CLR), U22.14 (VCC), U23.1 (1CLR), U23.4 (1PRE), U23.10 (2PRE), U23.13 (2CLR), U23.14 (VCC), U24.1 (1CLR), U24.4 (1PRE), U24.10 (2PRE), U24.13 (2CLR), U24.14 (VCC)
+15SW: C14.1, C93.1, C95.1, U10.16 (VDD), U11.16 (VDD), U142.1 (OUT)
+18V: C7.1, C17.1, C77.1, C79.1, C81.1, C83.1, C85.1, C87.1, C89.1, C91.1, C97.1, Q140.1 (E), U1.8 (V+), U2.4 (V+), U3.4 (V+), U4.4 (V+), U5.4 (V+), U6.4 (V+), U7.4 (V+), U8.4 (V+), U9.4 (V+), U12.4 (V+)
-15SW: C15.2, C94.2, C96.2, U10.5 (VSS), U11.5 (VSS), U143.3 (VO)
-18V: C11.2, C18.2, C78.2, C80.2, C82.2, C84.2, C86.2, C88.2, C90.2, C92.2, C98.2, Q141.1 (E), U1.4 (V-), U2.11 (V-), U3.11 (V-), U4.11 (V-), U5.11 (V-), U6.11 (V-), U7.11 (V-), U8.11 (V-), U9.11 (V-), U12.11 (V-)
AA1: C35.1, C36.1, R26.2, R27.1
AA2: C38.1, C39.1, R28.2, R29.1
AB1: C50.1, C51.1, R48.2, R49.1
AB2: C53.1, C54.1, R50.2, R51.1
AC1: C62.1, C63.1, R64.2, R65.1
AC2: C65.1, C66.1, R66.2, R67.1
AD1: C71.1, C72.1, R74.2, R75.1
AD2: C74.1, C75.1, R76.2, R77.1
ADJ+: C4.1, D1.2 (A), R1.2, R2.1, U140.1 (ADJ)
ADJ-: C8.2, D3.1 (K), R4.2, R5.1, U141.1 (ADJ)
AGND: C1.2, C2.1, C4.2, C5.2, C6.2, C7.2, C8.1, C9.1, C10.1, C11.1, C12.2, C13.1, C14.2, C15.1, C17.2, C18.1, C37.2, C40.2, C52.2, C55.2, C64.2, C67.2, C73.2, C76.2, C77.2, C78.1, C79.2, C80.1, C81.2, C82.1, C83.2, C84.1, C85.2, C86.1, C87.2, C88.1, C89.2, C90.1, C91.2, C92.1, C93.2, C94.1, C95.2, C96.1, C97.2, C98.1, J1.a13, J1.a14, J1.a15, J1.a16, J1.a17, J1.a18, J1.a19, J1.a20, J1.b3, J1.b6, J1.b9, J1.b12, J1.b15, J1.b18, J1.b21, J1.b24, J1.b27, J1.b30, R2.2, R5.2, R9.2, R11.2, R13.2, R15.2, R17.2, R19.2, R21.2, R23.2, R25.2, R31.2, R37.2, R43.2, R53.2, R59.2, R69.2, U1.3 (+), U4.10 (+), U4.12 (+), U5.3 (+), U5.5 (+), U5.10 (+), U5.12 (+), U6.10 (+), U6.12 (+), U7.3 (+), U7.5 (+), U8.3 (+), U8.5 (+), U9.3 (+), U9.5 (+), U9.10 (+), U9.12 (+), U10.4 (S1B), U10.6 (GND), U10.7 (S2B), U10.14 (S3B), U10.17 (S4B), U11.4 (S1B), U11.6 (GND), U11.7 (S2B), U11.8 (D2), U11.9 (S2A), U11.10 (IN2), U11.11 (IN3), U11.12 (S3A), U11.13 (D3), U11.14 (S3B), U11.17 (S4B), U11.18 (D4), U11.19 (S4A), U11.20 (IN4), U12.3 (+), U12.5 (+), U12.10 (+), U12.12 (+), U13.4 (2IN-), U13.6 (1IN-), U13.8 (3IN-), U13.10 (4IN-), U14.5 (2IN+), U14.6 (1IN-), U14.9 (3IN+), U14.11 (4IN+), U142.2 (GND), U143.1 (GND)
AH1: C19.2, C20.1, R10.1
AH1b: C21.2, C22.1, R12.1
AH2: C23.2, C24.1, R14.1
AH2b: C25.2, C26.1, R16.1
AH3: C27.2, C28.1, R18.1
AH3b: C29.2, C30.1, R20.1
AH4: C31.2, C32.1, R22.1
AH4b: C33.2, C34.1, R24.1
BA1: C37.1, R27.2, U4.3 (+)
BA2: C40.1, R29.2, U4.5 (+)
BASE+: C6.1, Q140.3 (B), R3.2
BASE-: C10.2, Q141.3 (B), R6.2
BB1: C52.1, R49.2, U6.3 (+)
BB2: C55.1, R51.2, U6.5 (+)
BC1: C64.1, R65.2, U7.10 (+)
BC2: C67.1, R67.2, U7.12 (+)
BD1: C73.1, R75.2, U8.10 (+)
BD2: C76.1, R77.2, U8.12 (+)
BH1: C20.2, R11.1, U2.3 (+)
BH1b: C22.2, R13.1, U2.5 (+)
BH2: C24.2, R15.1, U2.10 (+)
BH2b: C26.2, R17.1, U2.12 (+)
BH3: C28.2, R19.1, U3.3 (+)
BH3b: C30.2, R21.1, U3.5 (+)
BH4: C32.2, R23.1, U3.10 (+)
BH4b: C34.2, R25.1, U3.12 (+)
BPP1: C43.2, R32.2, R34.1, U4.8
BPP2: C46.2, R38.2, R40.1, U5.1
BPP3: C49.2, R44.2, R46.1, U5.8
BPP4: C58.2, R54.2, R56.1, U6.8
BPP5: C61.2, R60.2, R62.1, U7.1
BPP6: C70.2, R70.2, R72.1, U8.1
CHASSIS: H1.1, H2.1, H3.1, J1.a25, J1.a26
CI1: D5.1 (K), D6.2 (A), R89.2, R90.2, U13.7 (1IN+)
CI2: D10.1 (K), D11.2 (A), R97.2, R98.2, U13.5 (2IN+)
CI3: D15.1 (K), D16.2 (A), R105.2, R106.2, U13.9 (3IN+)
CI4: D20.1 (K), D21.2 (A), R113.2, R114.2, U13.11 (4IN+)
CI5: D25.1 (K), D26.2 (A), R121.2, R122.2, U14.7 (1IN+)
CK1: D8.1 (K), D9.1 (K), R94.1, U22.3 (1CLK)
CK2: D13.1 (K), D14.1 (K), R102.1, U22.11 (2CLK)
CK3: D18.1 (K), D19.1 (K), R110.1, U23.3 (1CLK)
CK4: D23.1 (K), D24.1 (K), R118.1, U23.11 (2CLK)
CK5: D28.1 (K), D29.1 (K), R126.1, U24.3 (1CLK)
CTRL_GND: C3.2, C99.2, C100.2, C101.2, C102.2, C103.2, C104.2, C105.2, C106.2, C107.2, C108.2, C109.2, C110.2, C111.2, C112.2, C113.2, C114.2, C115.2, C116.2, C117.2, C118.2, C119.2, C120.2, C121.2, C122.2, C123.2, C124.2, C125.2, D5.2 (A), D10.2 (A), D15.2 (A), D20.2 (A), D25.2 (A), J1.a23, J1.a24, J1.c16, J1.c20, J1.c24, J1.c28, J2.6, R94.2, R102.2, R110.2, R118.2, R126.2, U13.12 (GND), U14.4 (2IN-), U14.8 (3IN-), U14.10 (4IN-), U14.12 (GND), U15.7 (GND), U16.7 (GND), U17.7 (GND), U18.7 (GND), U18.12 (4A), U18.13 (4B), U19.7 (GND), U20.7 (GND), U21.7 (GND), U21.9 (4A), U21.11 (5A), U21.13 (6A), U22.7 (GND), U23.7 (GND), U24.7 (GND), U24.11 (2CLK), U24.12 (2D)
DJBUS_R: C16.2, J1.b2, R7.2, U1.2 (-)
G_HIGH: R85.1, U10.18 (D4)
G_KICK: R83.1, U10.8 (D2)
G_MID: R84.1, U10.13 (D3)
G_SUB: R82.1, U10.3 (D1)
G_SUPER: R86.1, U11.3 (D1)
HIGH: C74.2, C75.2, R113.1, U8.13 (-), U8.14, U10.19 (S4A)
KD1: C101.1, R96.2, U15.4 (2A), U22.2 (1D)
KD2: C104.1, R104.2, U16.1 (1A), U22.12 (2D)
KD3: C107.1, R112.2, U16.12 (4A), U23.2 (1D)
KD4: C110.1, R120.2, U17.9 (3A), U23.12 (2D)
KD5: C113.1, R128.2, U18.4 (2A), U24.2 (1D)
KICK: R63.2, R97.1, U7.7, U10.9 (S2A)
KQ1: U10.1 (IN1), U15.5 (2B), U22.5 (1Q)
KQ2: U10.10 (IN2), U16.2 (1B), U22.9 (2Q)
KQ3: U10.11 (IN3), U16.13 (4B), U23.5 (1Q)
KQ4: U10.20 (IN4), U17.10 (3B), U23.9 (2Q)
KQ5: U11.1 (IN1), U18.5 (2B), U24.5 (1Q)
KSW1: J2.1, R95.2, R96.1
KSW2: J2.2, R103.2, R104.1
KSW3: J2.3, R111.2, R112.1
KSW4: J2.4, R119.2, R120.1
KSW5: J2.5, R127.2, R128.1
MID: R81.2, R105.1, U9.7, U10.12 (S3A)
MID_O: R73.2, R80.1, U8.7
MIS1: D7.1 (K), R93.1, U15.6 (2Y)
MIS2: D12.1 (K), R101.1, U16.3 (1Y)
MIS3: D17.1 (K), R109.1, U16.11 (4Y)
MIS4: D22.1 (K), R117.1, U17.8 (3Y)
MIS5: D27.1 (K), R125.1, U18.6 (2Y)
N1P1: C41.1, C42.1, C43.1, R30.2, R31.1
N1P2: C44.1, C45.1, C46.1, R36.2, R37.1
N1P3: C47.1, C48.1, C49.1, R42.2, R43.1
N1P4: C56.1, C57.1, C58.1, R52.2, R53.1
N1P5: C59.1, C60.1, C61.1, R58.2, R59.1
N1P6: C68.1, C69.1, C70.1, R68.2, R69.1
NAP1: R33.2, R34.2, R35.1, U4.13 (-)
NAP2: R39.2, R40.2, R41.1, U5.6 (-)
NAP3: R45.2, R46.2, R47.1, U5.13 (-)
NAP4: R55.2, R56.2, R57.1, U6.13 (-)
NAP5: R61.2, R62.2, R63.1, U7.6 (-)
NAP6: R71.2, R72.2, R73.1, U8.6 (-)
NIMID: R80.2, R81.1, U9.6 (-)
NISUB: R78.2, R79.1, U9.2 (-)
NMP1: C41.2, C42.2, R32.1, U4.9 (-)
NMP2: C44.2, C45.2, R38.1, U5.2 (-)
NMP3: C47.2, C48.2, R44.1, U5.9 (-)
NMP4: C56.2, C57.2, R54.1, U6.9 (-)
NMP5: C59.2, C60.2, R60.1, U7.2 (-)
NMP6: C68.2, C69.2, R70.1, U8.2 (-)
NPAD: R8.2, R9.1, U1.5 (+)
NSUM: R82.2, R83.2, R84.2, R85.2, R86.2, R87.1, U12.2 (-)
NU9_1: U9.8, U9.9 (-)
NU9_2: U9.13 (-), U9.14
NU12_1: U12.6 (-), U12.7
NU12_2: U12.8, U12.9 (-)
NU12_3: U12.13 (-), U12.14
PZ1: D8.2 (A), U15.3 (1Y)
PZ2: D13.2 (A), U15.11 (4Y)
PZ3: D18.2 (A), U16.8 (3Y)
PZ4: D23.2 (A), U17.6 (2Y)
PZ5: D28.2 (A), U18.3 (1Y)
R1: C21.1, R10.2, U2.1, U2.2 (-)
R1B: C23.1, R12.2, R48.1, U2.6 (-), U2.7
R2: C25.1, R14.2, U2.8, U2.9 (-)
R2B: C27.1, R16.2, R64.1, U2.13 (-), U2.14
R3: C29.1, R18.2, U3.1, U3.2 (-)
R3B: C31.1, R20.2, R74.1, U3.6 (-), U3.7
R4: C33.1, R22.2, U3.8, U3.9 (-)
RAW+22: FB3.1, J1.a5, J1.a6
RAW+27: FB1.1, J1.a1, J1.a2
RAW-22: FB4.1, J1.a7, J1.a8
RAW-27: FB2.1, J1.a3, J1.a4
RX: C16.1, R7.1, R8.1, U1.1
S1A: C35.2, C36.2, R28.1, U4.1, U4.2 (-)
S1B: C38.2, C39.2, R30.1, R33.1, U4.6 (-), U4.7
S1C: R35.2, R36.1, R39.1, U4.14
S1D: R41.2, R42.1, R45.1, U5.7
S2B: C50.2, C51.2, R50.1, U6.1, U6.2 (-)
S2C: C53.2, C54.2, R52.1, R55.1, U6.6 (-), U6.7
S2D: R57.2, R58.1, R61.1, U6.14
S3C: C62.2, C63.2, R66.1, U7.8, U7.9 (-)
S3D: C65.2, C66.2, R68.1, R71.1, U7.13 (-), U7.14
S4C: C71.2, C72.2, R76.1, U8.8, U8.9 (-)
SUB: R79.2, R89.1, U9.1, U10.2 (S1A)
SUB_O: R47.2, R78.1, U5.14
SUPER: R24.2, R121.1, U3.13 (-), U3.14, U11.2 (S1A)
TO1: D9.2 (A), U15.8 (3Y)
TO2: D14.2 (A), U16.6 (2Y)
TO3: D19.2 (A), U17.3 (1Y)
TO4: D24.2 (A), U17.11 (4Y)
TO5: D29.2 (A), U18.8 (3Y)
TON1: U15.9 (3A), U19.6 (3Y)
TON2: U16.4 (2A), U19.12 (6Y)
TON3: U17.1 (1A), U20.6 (3Y)
TON4: U17.12 (4A), U20.12 (6Y)
TON5: U18.9 (3A), U21.6 (3Y)
TR1: C100.1, D7.2 (A), R93.2, U19.5 (3A)
TR2: C103.1, D12.2 (A), R101.2, U19.13 (6A)
TR3: C106.1, D17.2 (A), R109.2, U20.5 (3A)
TR4: C109.1, D22.2 (A), R117.2, U20.13 (6A)
TR5: C112.1, D27.2 (A), R125.2, U21.5 (3A)
V22F+: C12.1, FB3.2, U142.3 (IN)
V22F-: C13.2, FB4.2, U143.2 (VI)
V27F+: C1.1, D2.1 (K), FB1.2, U140.3 (VI)
V27F-: C2.2, D4.2 (A), FB2.2, U141.2 (VI)
VPAD: C19.1, R26.1, U1.6 (-), U1.7
VREG+: C5.1, D1.1 (K), D2.2 (A), Q140.2 (C), R1.1, R3.1, U140.2 (VO)
VREG-: C9.2, D3.2 (A), D4.1 (K), Q141.2 (C), R4.1, R6.1, U141.3 (VO)
VSUM: R87.2, R88.1, U12.1
ZC1: R90.1, R91.2, R92.1, U13.1 (1OUT), U15.1 (1A)
ZC2: R98.1, R99.2, R100.1, U13.2 (2OUT), U15.12 (4A)
ZC3: R106.1, R107.2, R108.1, U13.14 (3OUT), U16.9 (3A)
ZC4: R114.1, R115.2, R116.1, U13.13 (4OUT), U17.4 (2A)
ZC5: R122.1, R123.2, R124.1, U14.1 (1OUT), U18.1 (1A)
ZCX1: R129.2, U14.2 (2OUT)
ZCX2: R130.2, U14.14 (3OUT)
ZCX3: R131.2, U14.13 (4OUT)
ZD1: U15.2 (1B), U19.4 (2Y)
ZD2: U15.13 (4B), U19.10 (5Y)
ZD3: U16.10 (3B), U20.4 (2Y)
ZD4: U17.5 (2B), U20.10 (5Y)
ZD5: U18.2 (1B), U21.4 (2Y)
ZN1: U19.2 (1Y), U19.3 (2A)
ZN2: U19.8 (4Y), U19.11 (5A)
ZN3: U20.2 (1Y), U20.3 (2A)
ZN4: U20.8 (4Y), U20.11 (5A)
ZN5: U21.2 (1Y), U21.3 (2A)
ZR1: C99.1, R92.2, U19.1 (1A)
ZR2: C102.1, R100.2, U19.9 (4A)
ZR3: C105.1, R108.2, U20.1 (1A)
ZR4: C108.1, R116.2, U20.9 (4A)
ZR5: C111.1, R124.2, U21.1 (1A)

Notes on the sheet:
BACKPLANE C96 (classe 5-WAY, sistema-backplane §4)
ALIMENTAZIONE +-18 audio, +-15 switch, +5, +-15 LN, +-5 riferimento
INGRESSO: ricevitore del DJ bus (inverte) e pad -6 dB (§2, REV todo 227)
BANCA allineata agli incroci H 60/250/1,2k/8k (§3.2bis, bank-aligned-h.cir)
KILL a pi greco (ADG1434) e somma delle 5 vie (§8.10)
KILL allo zero della via: LM339, 74HC86, 74HC14, 74HC74 (RISULTATI-kill-zc.md, dec. 164)
CAVO SCHEDA COMANDI (J2)
